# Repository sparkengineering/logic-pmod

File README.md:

# logic-pmod

[![View with - KiCanvas](https://img.shields.io/badge/KiCanvas-b187ff?label=View%20with
)](https://kicanvas.org/?github=https%3A%2F%2Fgithub.com%2Fsparkengineering%2Flogic-pmod)

## Description

Logic level shifter with Digilent Pmod™ interface for use as logic analyzer.

- 8 fixed direction, length tuned, level shifting channels
- Up/down translation from 1.8V, 2.5V, 5V to 3.3V
- Bus Pirate probe cable compatible 10-pin connector

## Contents

| File                                           | Description             |
|------------------------------------------------|-------------------------|
| [logic-pmod.pdf](./logic-pmod.pdf)             | Schematic in PDF format |
| [logic-pmod.csv](./logic-pmod.csv)             | BOM in CSV format       |
| [logic-pmod.png](./logic-pmod.png)             | PCB 3D render           |
|                                                |                         |
| [logic-pmod.kicad_pro](./logic-pmod.kicad_pro) | KiCad 8.0.0 project     |
| [logic-pmod.kicad_pcb](./logic-pmod.kicad_pcb) | KiCad 8.0.0 PCB         |
| [logic-pmod.kicad_sch](./logic-pmod.kicad_sch) | KiCad 8.0.0 schematic   |

## Probe Pinout

| Pin | Color  | Net  |
|-----|--------|------|
|   1 | Brown  | GND  |
|   2 | Red    | +3V3 |
|     |        |      |
|   3 | Orange | CH5  |
|   4 | Yellow | CH1  |
|   5 | Green  | CH6  |
|   6 | Blue   | CH2  |
|   7 | Purple | CH7  |
|   8 | Grey   | CH3  |
|   9 | White  | CH8  |
|  10 | Black  | CH4  |

## Further Reading

- FPGA Logic Analyzer and GUI [^1]
- Small footprint and configurable embedded FPGA logic analyzer [^2]
- Integrated Logic Analyzer (ILA) [^3]

[^1]: https://github.com/lekgolo167/enxor-logic-analyzer
[^2]: https://github.com/enjoy-digital/litescope
[^3]: https://www.xilinx.com/products/intellectual-property/ila.html

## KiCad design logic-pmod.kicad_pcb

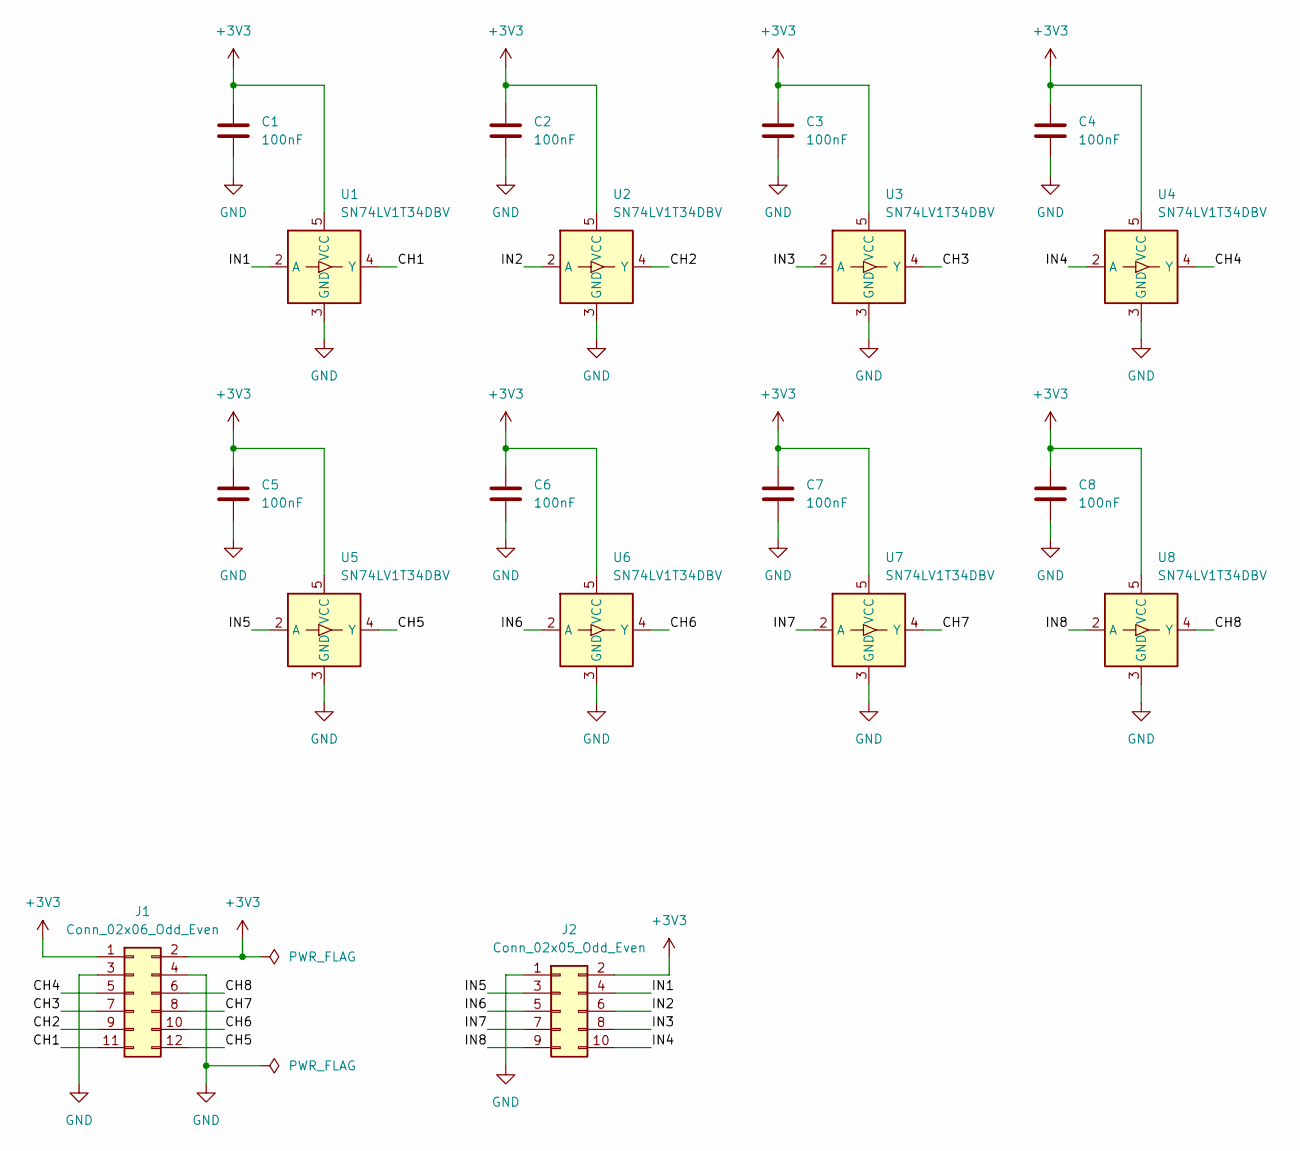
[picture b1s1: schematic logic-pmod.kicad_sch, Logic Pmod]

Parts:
C1, C2, C3, C4, C5, C6, C7, C8: 100nF; C_0402_1005Metric; MPN GRM155R61A104JA01D
J1: Conn_02x06_Odd_Even; PinHeader_2x06_P2.54mm_Horizontal; MPN 826634-6
J2: Conn_02x05_Odd_Even; IDC-Header_2x05_P2.54mm_Vertical; MPN 1761681-3
U1, U2, U3, U4, U5, U6, U7, U8: SN74LV1T34DBV; SOT-23-5; MPN SN74LV1T34QDBVRQ1

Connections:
+3V3: C1.1, C2.1, C3.1, C4.1, C5.1, C6.1, C7.1, C8.1, J1.1, J1.2, J2.2, U1.5 (VCC), U2.5 (VCC), U3.5 (VCC), U4.5 (VCC), U5.5 (VCC), U6.5 (VCC), U7.5 (VCC), U8.5 (VCC)
/CH1: J1.11, U1.4 (Y)
/CH2: J1.9, U2.4 (Y)
/CH3: J1.7, U3.4 (Y)
/CH4: J1.5, U4.4 (Y)
/CH5: J1.12, U5.4 (Y)
/CH6: J1.10, U6.4 (Y)
/CH7: J1.8, U7.4 (Y)
/CH8: J1.6, U8.4 (Y)
/IN1: J2.4, U1.2 (A)
/IN2: J2.6, U2.2 (A)
/IN3: J2.8, U3.2 (A)
/IN4: J2.10, U4.2 (A)
/IN5: J2.3, U5.2 (A)
/IN6: J2.5, U6.2 (A)
/IN7: J2.7, U7.2 (A)
/IN8: J2.9, U8.2 (A)
GND: C1.2, C2.2, C3.2, C4.2, C5.2, C6.2, C7.2, C8.2, J1.3, J1.4, J2.1, U1.3 (GND), U2.3 (GND), U3.3 (GND), U4.3 (GND), U5.3 (GND), U6.3 (GND), U7.3 (GND), U8.3 (GND)

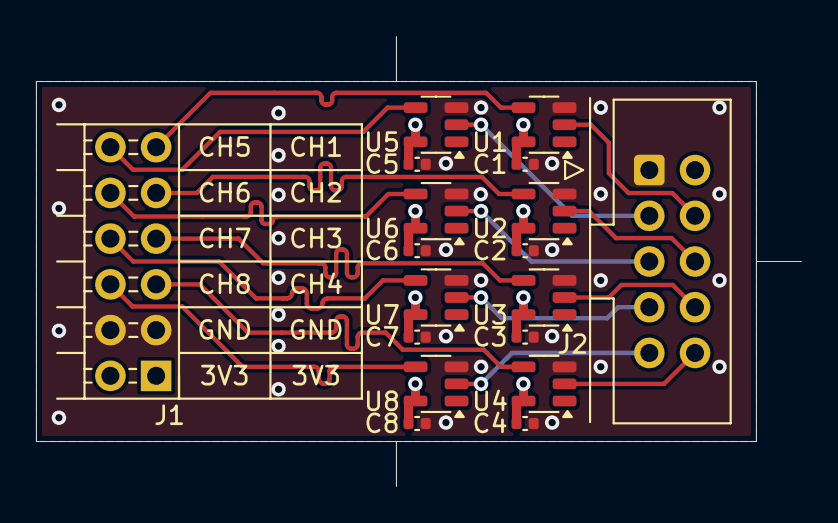
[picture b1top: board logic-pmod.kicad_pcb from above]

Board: 4 copper layers, 42.5 x 25.0 mm, 18 parts (0 on the bottom side), 18 nets.
